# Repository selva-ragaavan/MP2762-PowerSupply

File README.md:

# MP2762-PowerSupply
The MPS2762 is a Power Delivery (PD) design intended to deliver a stable 25W load while charging a 2S Li-ion battery, using the MPS2762 IC along with a CH224K for PD voltage handshaking.

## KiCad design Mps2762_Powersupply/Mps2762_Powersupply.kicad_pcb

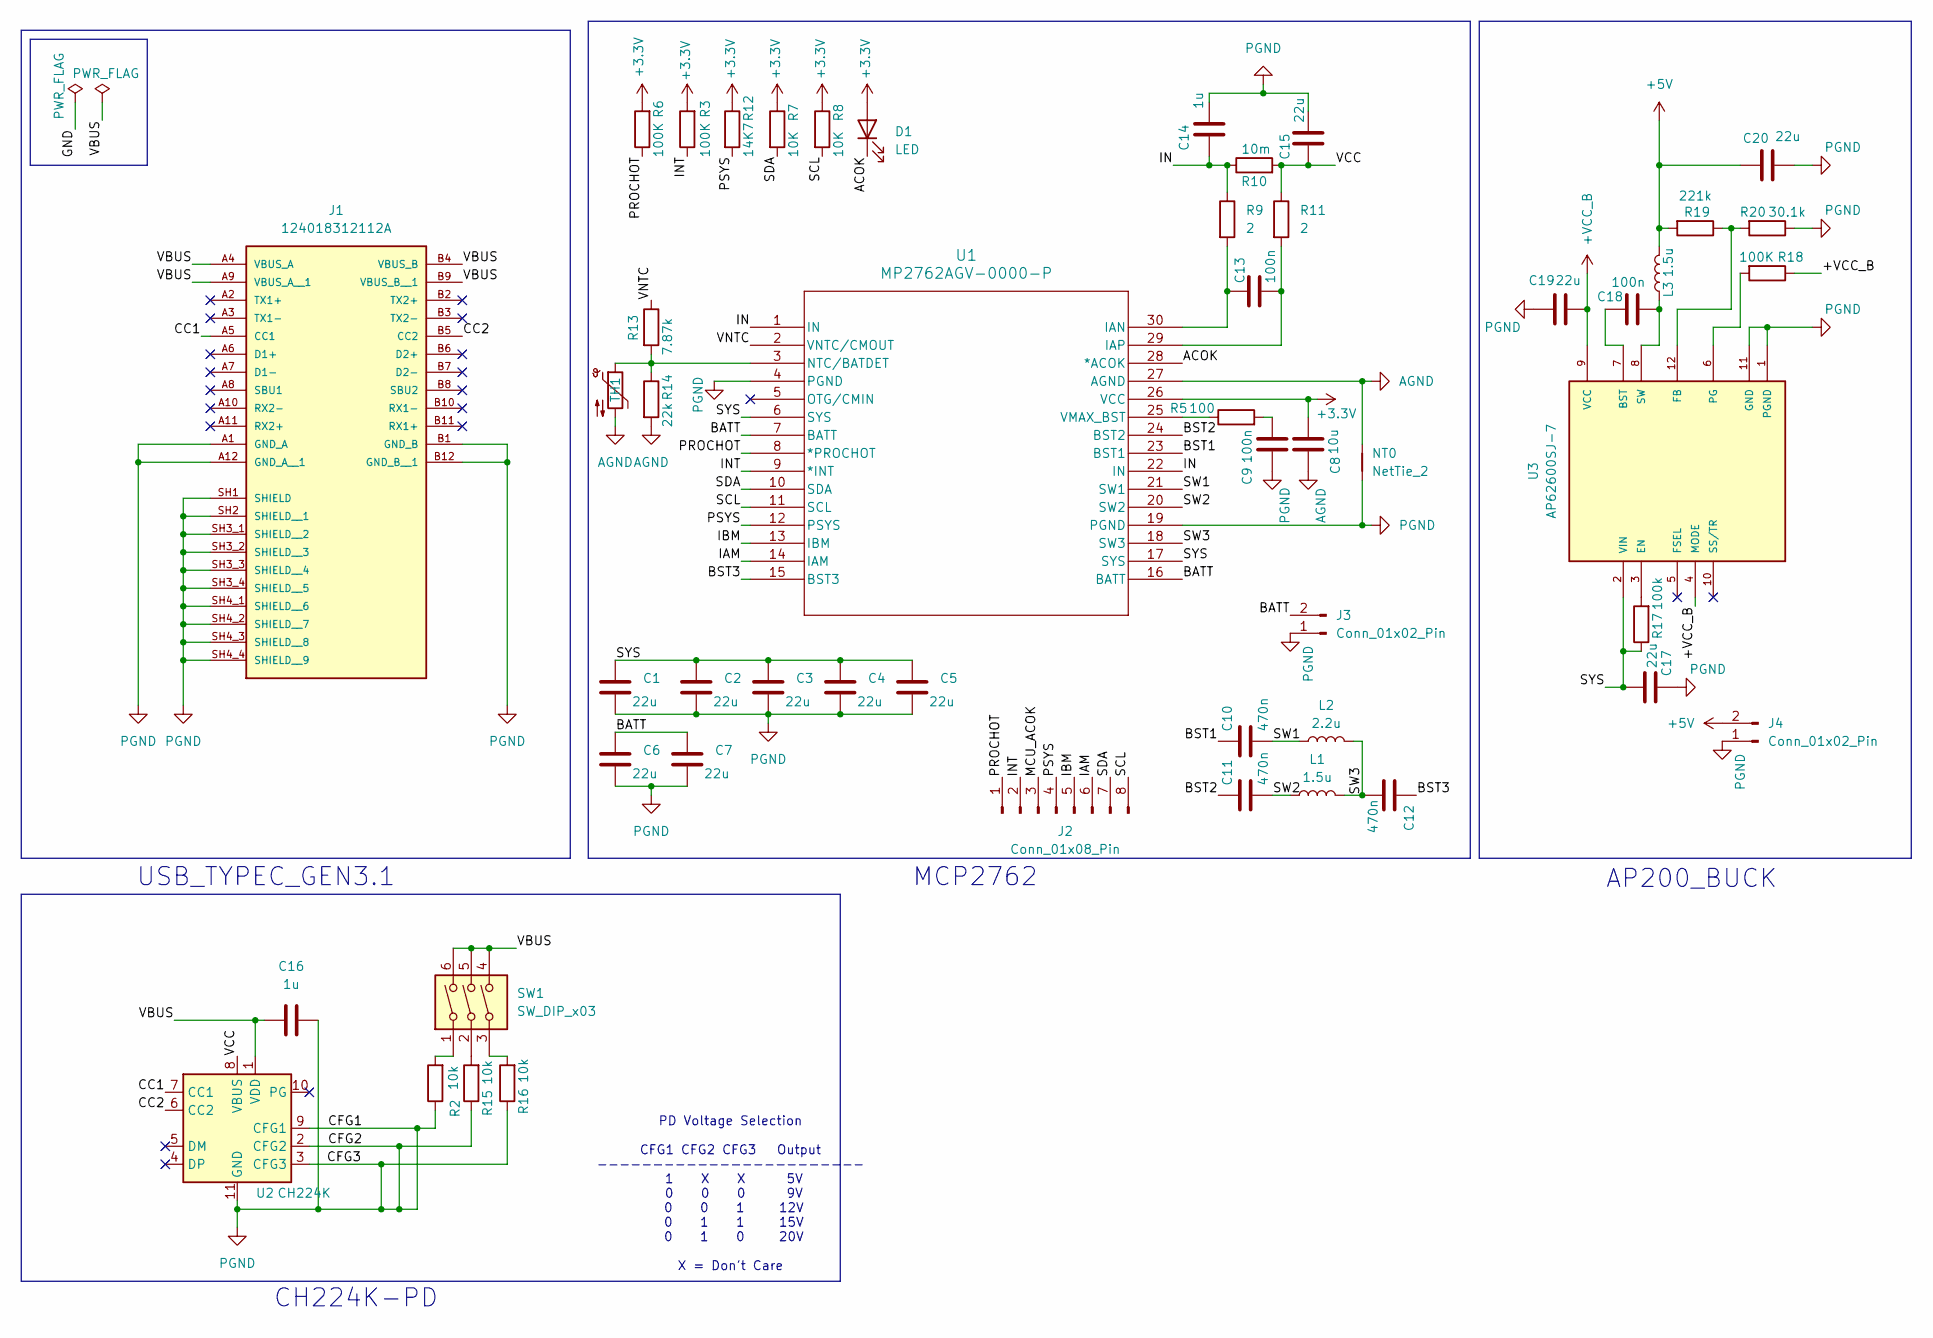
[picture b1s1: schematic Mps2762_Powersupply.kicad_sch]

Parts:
C1, C2, C3, C4, C5, C6, C7, C15: 22u; C_0805_2012Metric
C8: 10u; C_0201_0603Metric
C9, C13: 100n; C_0201_0603Metric
C10, C11, C12: 470n; C_0201_0603Metric
C14, C16: 1u; C_0201_0603Metric
C17, C19, C20: 22u; C_0201_0603Metric
C18: 100n; C_0402_1005Metric
D1: LED; LED_0201_0603Metric
J1: 124018312112A; AMPHENOL_124018312112A; PARTREV 1
J2: Conn_01x08_Pin; JST_PH_B8B-PH-K_1x08_P2.00mm_Vertical
J3, J4: Conn_01x02_Pin; Hirose_DF13-02P-1.25DSA_1x02_P1.25mm_Vertical
L1, L3: 1.5u; XGL4030-152MEC
L2: 2.2u; IND_XAL5030-222MEC_COC
NT0: NetTie_2; NetTie-2_SMD_Pad0.5mm
R2, R15, R16: 10k; R_0201_0603Metric
R3, R6, R18: 100K; R_0201_0603Metric
R5: 100; R_0805_2012Metric
R7, R8: 10K; R_0201_0603Metric
R9, R11: 2; R_0201_0603Metric
R10: 10m; R_1206_3216Metric
R12: 14K7; R_0201_0603Metric
R13: 7.87k; R_0201_0603Metric
R14: 22k; R_0201_0603Metric
R17: 100k; R_0201_0603Metric
R19: 221k; R_0201_0603Metric
R20: 30.1k; R_0201_0603Metric
SW1: SW_DIP_x03; SW_DIP_SPSTx03_Slide_6.7x9.18mm_W8.61mm_P2.54mm_LowProfile
TH1: Thermistor_NTC; R_0402_1005Metric
U1: MP2762AGV-0000-P; QFN-30_MP2762A_MNP
U2: CH224K; SSOP-10-1EP_3.9x4.9mm_P1mm_EP2.1x3.3mm_ThermalVias
U3: AP62600SJ-7; IC_AP62600SJ-7; PARTREV 2 - 2

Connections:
+3.3V: C8.1, D1.2 (A), R3.2, R6.2, R7.1, R8.1, R12.1, U1.26 (VCC)
+5V: C20.2, J4.2, L3.2, R19.2
+VCC_B: C19.1, R18.1, U3.4 (MODE), U3.9 (VCC)
/ACOK: D1.1 (K), U1.28 (*ACOK)
/BATT: C6.1, C7.1, J3.2, U1.7 (BATT), U1.16 (BATT)
/BST1: C10.1, U1.23 (BST1)
/BST2: C11.1, U1.24 (BST2)
/BST3: C12.1, U1.15 (BST3)
/CC1: J1.A5 (CC1), U2.7 (CC1)
/CC2: J1.B5 (CC2), U2.6 (CC2)
/IAM: J2.6, U1.14 (IAM)
/IBM: J2.5, U1.13 (IBM)
/IN: C14.1, R9.1, R10.1, U1.1 (IN), U1.22 (IN)
/INT: J2.2, R3.1, U1.9 (*INT)
/MCU_ACOK: J2.3
/PROCHOT: J2.1, R6.1, U1.8 (*PROCHOT)
/PSYS: J2.4, R12.2, U1.12 (PSYS)
/SCL: J2.8, R8.2, U1.11 (SCL)
/SDA: J2.7, R7.2, U1.10 (SDA)
/SW1: C10.2, L2.1, U1.21 (SW1)
/SW2: C11.2, L1.1, U1.20 (SW2)
/SW3: C12.2, L1.2, L2.2, U1.18 (SW3)
/SYS: C1.1, C2.1, C3.1, C4.1, C5.1, C17.2, R17.1, U1.6 (SYS), U1.17 (SYS), U3.2 (VIN)
/VBUS: C16.2, J1.A4 (VBUS_A), J1.A9 (VBUS_A__1), J1.B4 (VBUS_B), J1.B9 (VBUS_B__1), SW1.4, SW1.5, SW1.6, U2.1 (VDD)
/VCC: C15.1, R10.2, R11.1, U2.8 (VBUS)
/VNTC: R13.1, U1.2 (VNTC/CMOUT)
AGND: C8.2, NT0.2, R14.2, TH1.2, U1.27 (AGND)
unnamed: C9.1, R5.2
unnamed: R2.2, SW1.1
unnamed: R15.2, SW1.2
unnamed: R16.2, SW1.3
unnamed: C13.1, R9.2, U1.30 (IAN)
unnamed: C13.2, R11.2, U1.29 (IAP)
unnamed: R13.2, R14.1, TH1.1, U1.3 (NTC/BATDET)
unnamed: R5.1, U1.25 (VMAX_BST)
unnamed: C18.2, U3.7 (BST)
unnamed: R17.2, U3.3 (EN)
unnamed: R19.1, R20.2, U3.12 (FB)
unnamed: R18.2, U3.6 (PG)
unnamed: C18.1, L3.1, U3.8 (SW)
PGND: C1.2, C2.2, C3.2, C4.2, C5.2, C6.2, C7.2, C9.2, C14.2, C15.2, C16.1, C17.1, C19.2, C20.1, J1.A1 (GND_A), J1.A12 (GND_A__1), J1.B1 (GND_B), J1.B12 (GND_B__1), J1.SH1 (SHIELD), J1.SH2 (SHIELD__1), J1.SH3_1 (SHIELD__2), J1.SH3_2 (SHIELD__3), J1.SH3_3 (SHIELD__4), J1.SH3_4 (SHIELD__5), J1.SH4_1 (SHIELD__6), J1.SH4_2 (SHIELD__7), J1.SH4_3 (SHIELD__8), J1.SH4_4 (SHIELD__9), J3.1, J4.1, NT0.1, R2.1, R15.1, R16.1, R20.1, U1.4 (PGND), U1.19 (PGND), U2.2 (CFG2), U2.3 (CFG3), U2.9 (CFG1), U2.11 (GND), U3.1 (PGND), U3.11 (GND)

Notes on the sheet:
CH224K-PD
AP200_BUCK
MCP2762
PD Voltage Selection CFG1 CFG2 CFG3 Output ------------------------ 1 X X 5V 0 0 0 9V 0 0 1 12V 0 1 1 15V 0 1 0 20V X = Don't Care
USB_TYPEC_GEN3.1

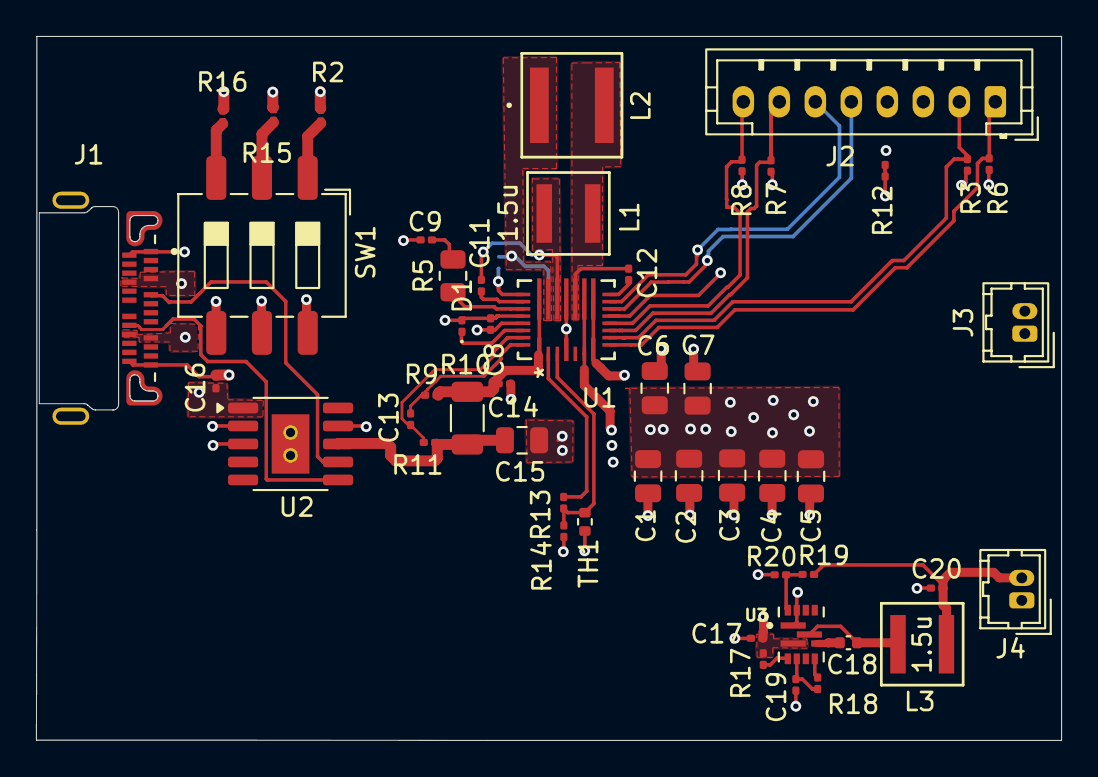
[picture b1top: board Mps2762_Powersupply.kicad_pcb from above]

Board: 4 copper layers, 57.0 x 39.1 mm, 51 parts (1 on the bottom side), 40 nets.

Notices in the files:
parts and their libraries:
Copyright 2016 Accelerated Designs. All rights reserved.
